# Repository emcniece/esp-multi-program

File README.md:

#ESP8266 Multi-Footprint Programming Jig

Fits multiple ESP8266 footprints.

Currently supported:

* 12e

Todo:

* ESP-01
* the others

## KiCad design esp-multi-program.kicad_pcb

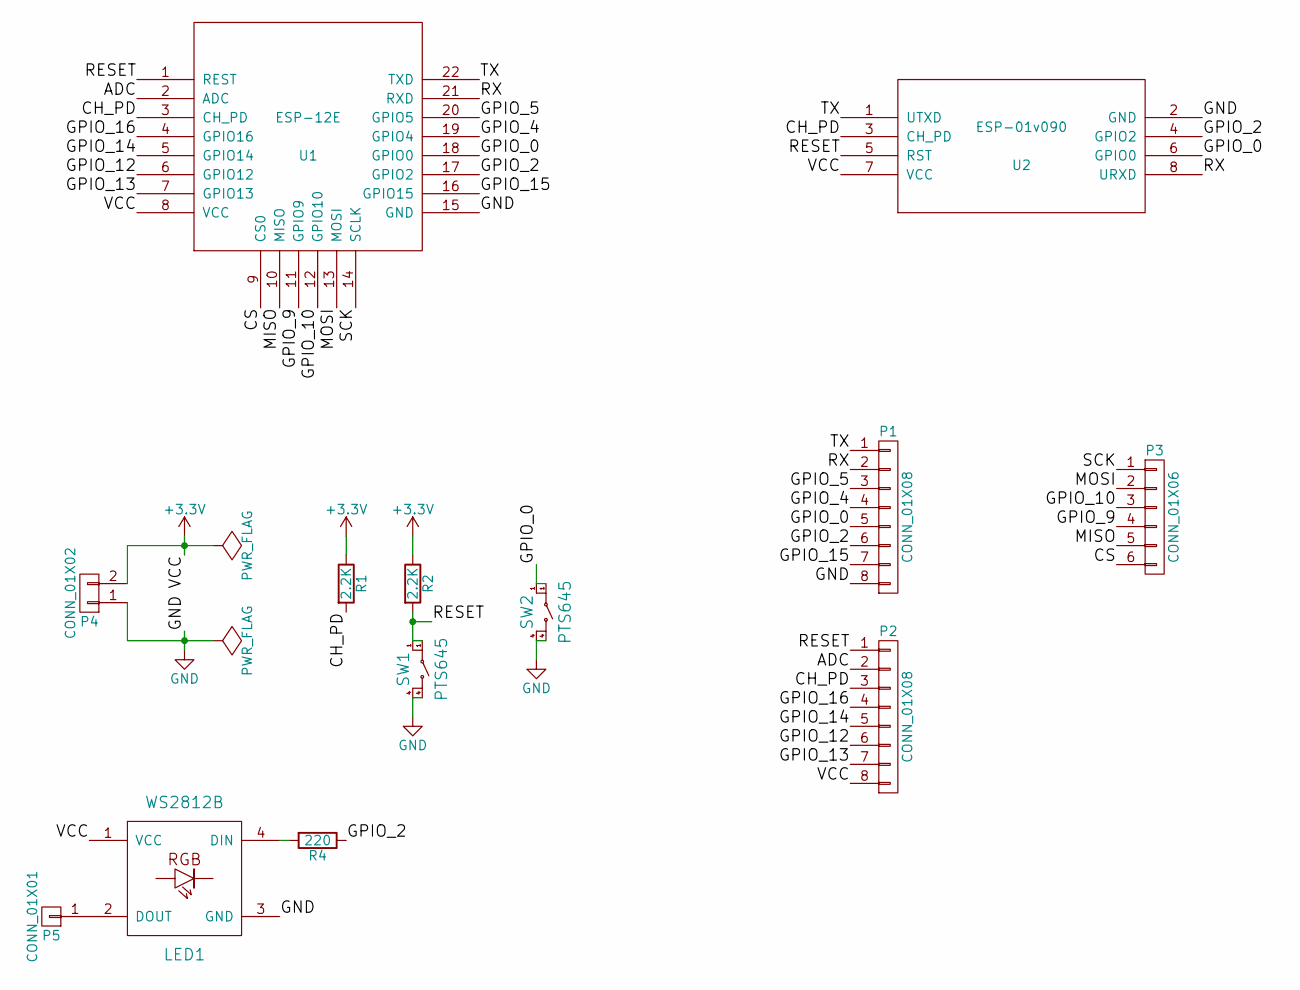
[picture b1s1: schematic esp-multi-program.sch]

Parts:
LED1: WS2812B
P1, P2: CONN_01X08; Pin_Header_Straight_1x08
P3: CONN_01X06; Pin_Header_Straight_1x06
P4: CONN_01X02; Pin_Header_Straight_1x02
P5: CONN_01X01; Pin_Header_Straight_1x01
R1, R2: 2.2K; R_0805_HandSoldering
R4: 220; R_0805_HandSoldering
SW1, SW2: PTS645
U1: ESP-12E
U2: ESP-01v090; ESP-01

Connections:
+3V3: LED1.1 (VCC), P2.8, P4.2, R1.1, R2.1, U1.8 (VCC), U2.7 (VCC)
/ADC: P2.2, U1.2 (ADC)
/CH_PD: P2.3, R1.2, U1.3 (CH_PD), U2.3 (CH_PD)
/CS: P3.6, U1.9 (CS0)
/GPIO_0: P1.5, SW2.1, U1.18 (GPIO0), U2.6 (GPIO0)
/GPIO_2: P1.6, R4.1, U1.17 (GPIO2), U2.4 (GPIO2)
/GPIO_4: P1.4, U1.19 (GPIO4)
/GPIO_5: P1.3, U1.20 (GPIO5)
/GPIO_9: P3.4, U1.11 (GPIO9)
/GPIO_10: P3.3, U1.12 (GPIO10)
/GPIO_12: P2.6, U1.6 (GPIO12)
/GPIO_13: P2.7, U1.7 (GPIO13)
/GPIO_14: P2.5, U1.5 (GPIO14)
/GPIO_15: P1.7, U1.16 (GPIO15)
/GPIO_16: P2.4, U1.4 (GPIO16)
/MISO: P3.5, U1.10 (MISO)
/MOSI: P3.2, U1.13 (MOSI)
/RESET: P2.1, R2.2, SW1.1, U1.1 (REST), U2.5 (RST)
/RX: P1.2, U1.21 (RXD), U2.8 (URXD)
/SCK: P3.1, U1.14 (SCLK)
/TX: P1.1, U1.22 (TXD), U2.1 (UTXD)
GND: LED1.3 (GND), P1.8, P4.1, SW1.4, SW2.4, U1.15 (GND), U2.2 (GND)
unnamed: LED1.2 (DOUT), P5.1
unnamed: LED1.4 (DIN), R4.2

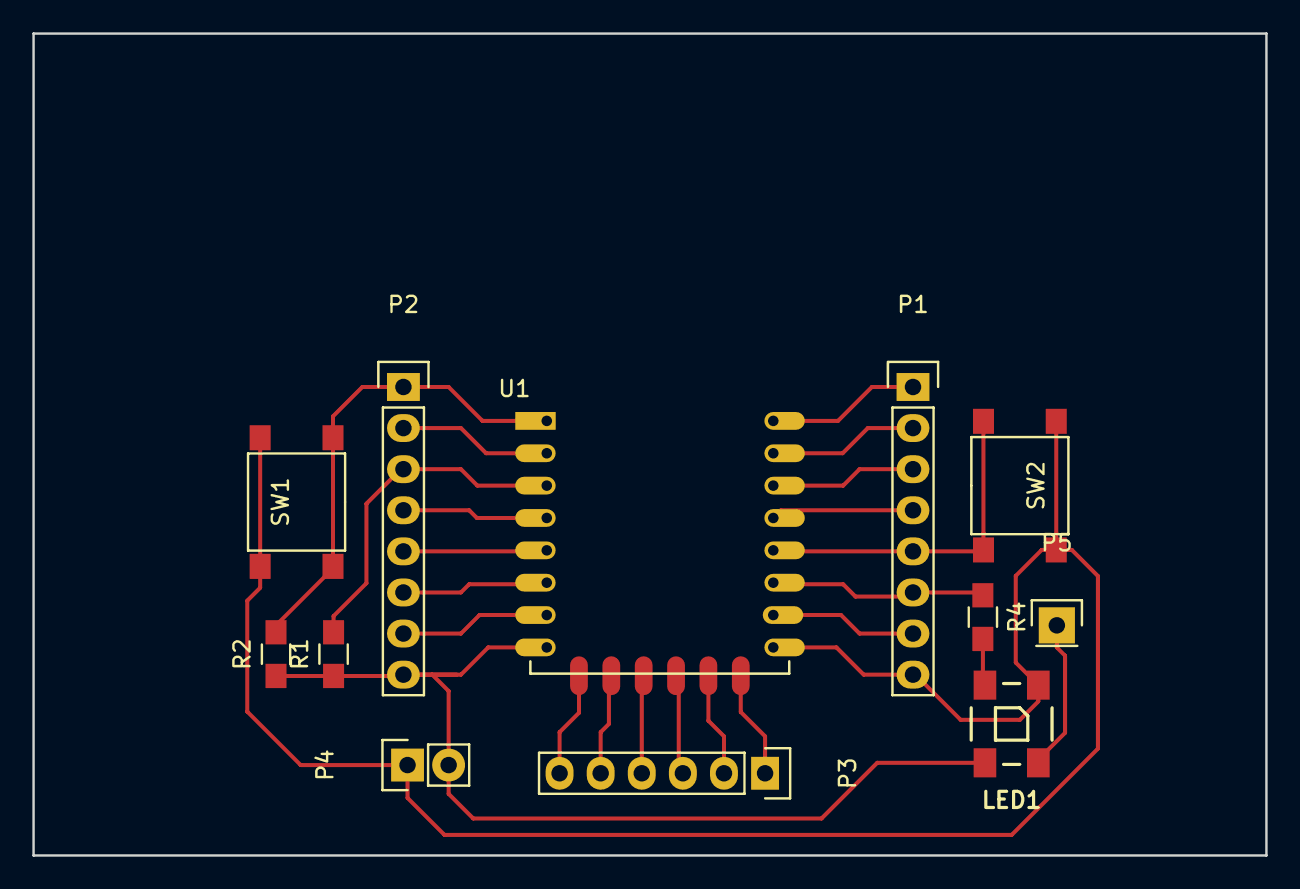
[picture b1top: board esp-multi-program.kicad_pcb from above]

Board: 2 copper layers, 76.2 x 50.8 mm, 12 parts (0 on the bottom side), 24 nets.

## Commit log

2016-09-17 Init: 12e footprint
2016-09-18 Fixing resistors and adding headers
